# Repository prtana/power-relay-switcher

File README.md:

# Power Relay Switcher

**Power Relay Switcher** is an electronic device consisting of **4 relays**, each of which is capable of switching loads of up to **20 A**, **240 V AC** or **28 V DC**. Each of the four relays can be **manually** closed/opened from the **front panel** or via **USB** using **SCPI** commands. 

The device was designed for the automation of running battery pack management unit learning cycles for batteries up to a capacity of 200 Ah. In that application it is to be used in conjunction with a power supply, an electronic load and a multimeter. These battery learning cycles require charging-resting-discharging-resting periods in excess of 24 hours which are cumbersome for an operator to manually manage having to connect and disconnect a power supply and an electronic load at the exact moments determined by the learning cycle.

## User's Guide

### Front Panel
On the front panel there is a main **ON-OFF** rocker switch and **two toggle switches: USB/Manual** and **Close/Open** together with **two status LEDs** per relay. 

#### USB/Manual Switch
The **USB/Manual** switch allows the operator to choose whether the relay ought to be operated via **USB** using **SCPI** commands or **manually**. 

- If the **USB/Manual** switch is at the **USB** position, the **Close/Open** switch is disabled. 
- If the **USB/Manual** switch is switched from **USB** to **Manual**, the relay will be set to the position determined by the **Close/Open** switch. 
- If the **USB/Manual** switch is switched from **Manual** to **USB**, the relay will remain in the position last set by the **Close/Open** switch until a new **SCPI** command is sent to close or open it.

#### Close/Open Switch
The **Close/Open** switch allows the operator to manually close and open the relay contacts if the **USB/Manual** switch is at the **Manual** position. 

#### Status LEDs
There are two status LEDs per relay which indicate whether the relay contacts are in the **Closed** or **Open** position. 

### Rear Panel
On the rear panel there are:
- **USB Type-B** socket for SCPI control
- **Terminal blocks** with plugs for connecting to the relays' **Normally Open** (NO) and **Common** (COM) pins
- **Cooling fan**
- **230 V AC** mains C14 socket

### SCPI
The following SCPI commands are supported:

- `*IDN?\n`
- `ROUTe:CLOSe (<channel list>)\n`
- `ROUTe:CLOSe? (<channel list>)\n`
- `ROUTe:OPEN (<channel list>)\n`
- `ROUTe:OPEN? (<channel list>)\n`

`<channel list>` is a list of relay channels to be switched or queried. It can be a single channel, i.e `2`, a comma seperated list, i.e `2,4` or a range, i.e `1:3`.

#### \*IDN?\n
- Device identification query.
- Returns the vendor, model, serial number and firmware version in comma seperated format.
- Example `*IDN?\n` returns `Deeply Embedded,Power Relay Switcher,0,0\n`.

#### ROUTe:CLOSe (\<channel list\>)\n
- Closes the relays specified by the `<channel list\>`.
- The relay's **USB/Manual** switch has to be set to **USB** in order to switch it using SCPI.
- Returns nothing.
- Example to close relays one and four: `ROUT:CLOS (1,4)\n`

#### ROUTe:CLOSe? (\<channel list\>)\n
- Queries whether the relays specified by the `<channel list\>` are closed.
- Returns the status of queried relays in a comma seperated form, where 1 - closed, 0 - open.
- Example to query relays one to four: `ROUT:CLOS? (1:4)\n`; returns in case if relay one is closed and two to four are open: `1,0,0,0\n`.

#### ROUTe:OPEN (\<channel list\>)\n
- Opens the relays specified by the `<channel list\>`. 
- The relay's **USB/Manual** switch has to be set to **USB** in order to switch it using SCPI.
- Returns nothing.
- Example to open relays one to three: `ROUT:OPEN (1:3)\n`.

#### ROUTe:OPEN? (\<channel list\>)\n
- Queries whether the relays specified by the `<channel list\>` are open.
- Returns the status of queried relays in a comma seperated form, where 1 - open, 0 - closed.
- Example to query relays one to four: `ROUT:OPEN? (1:4)\n`; returns in case if relay one is closed and two to four are open: `0,1,1,1\n`.

#### Usage Example
- Determine the COM port in use.
- Use your preferred terminal program. In this case **PUTTY** is used, the COM port is `/dev/ttyACM1` and baudrate is selected `115200`. 

- For PUTTY, make sure to select `Force on` for `Local echo` and `Local line editing` to see the typed text and to send the whole line at once rather than character by character.

- Example comminucation is as follows. Note that a newline character `\n` can be entered in PUTTY by `Ctrl + J` and is displayed as `^J`.

## Project Overview

### Firmware
The C code for the STM32L062K8Tx microcontroller is in the [/firmware/power-relay-switcher](https://github.com/prtana/power-relay-switcher/tree/main/firmware/power-relay-switcher) directory.

### Hardware
There are relevant files in the [/hardware](https://github.com/prtana/power-relay-switcher/tree/main/hardware) directory for the three PCBs: the main PCB and the aluminium front and back panels.

#### Main PCB
For the main PCB the following resources are available:
- [3D step model](https://github.com/prtana/power-relay-switcher/tree/main/hardware/PRS_relay_board/3D)
- [Bill of materials](https://github.com/prtana/power-relay-switcher/tree/main/hardware/PRS_relay_board/BOM)
- [KiCad project](https://github.com/prtana/power-relay-switcher/tree/main/hardware/PRS_relay_board/KiCad)
- [Gerber files](https://github.com/prtana/power-relay-switcher/tree/main/hardware/PRS_relay_board/Gerbers)
- [PDF schematic](https://github.com/prtana/power-relay-switcher/blob/main/hardware/PRS_relay_board/PRS_relay_board.pdf)

#### Front Panel
For the aluminium front panel the following resources are available:
- [3D step model](https://github.com/prtana/power-relay-switcher/tree/main/hardware/PRS_front_panel/3D)
- [KiCad project](https://github.com/prtana/power-relay-switcher/tree/main/hardware/PRS_front_panel/KiCad)
- [Gerber files](https://github.com/prtana/power-relay-switcher/tree/main/hardware/PRS_front_panel/Gerbers)

#### Rear Panel
For the aluminium rear panel the following resources are available:
- [3D step model](https://github.com/prtana/power-relay-switcher/tree/main/hardware/PRS_rear_panel/3D)
- [KiCad project](https://github.com/prtana/power-relay-switcher/tree/main/hardware/PRS_rear_panel/KiCad)
- [Gerber files](https://github.com/prtana/power-relay-switcher/tree/main/hardware/PRS_rear_panel/Gerbers)

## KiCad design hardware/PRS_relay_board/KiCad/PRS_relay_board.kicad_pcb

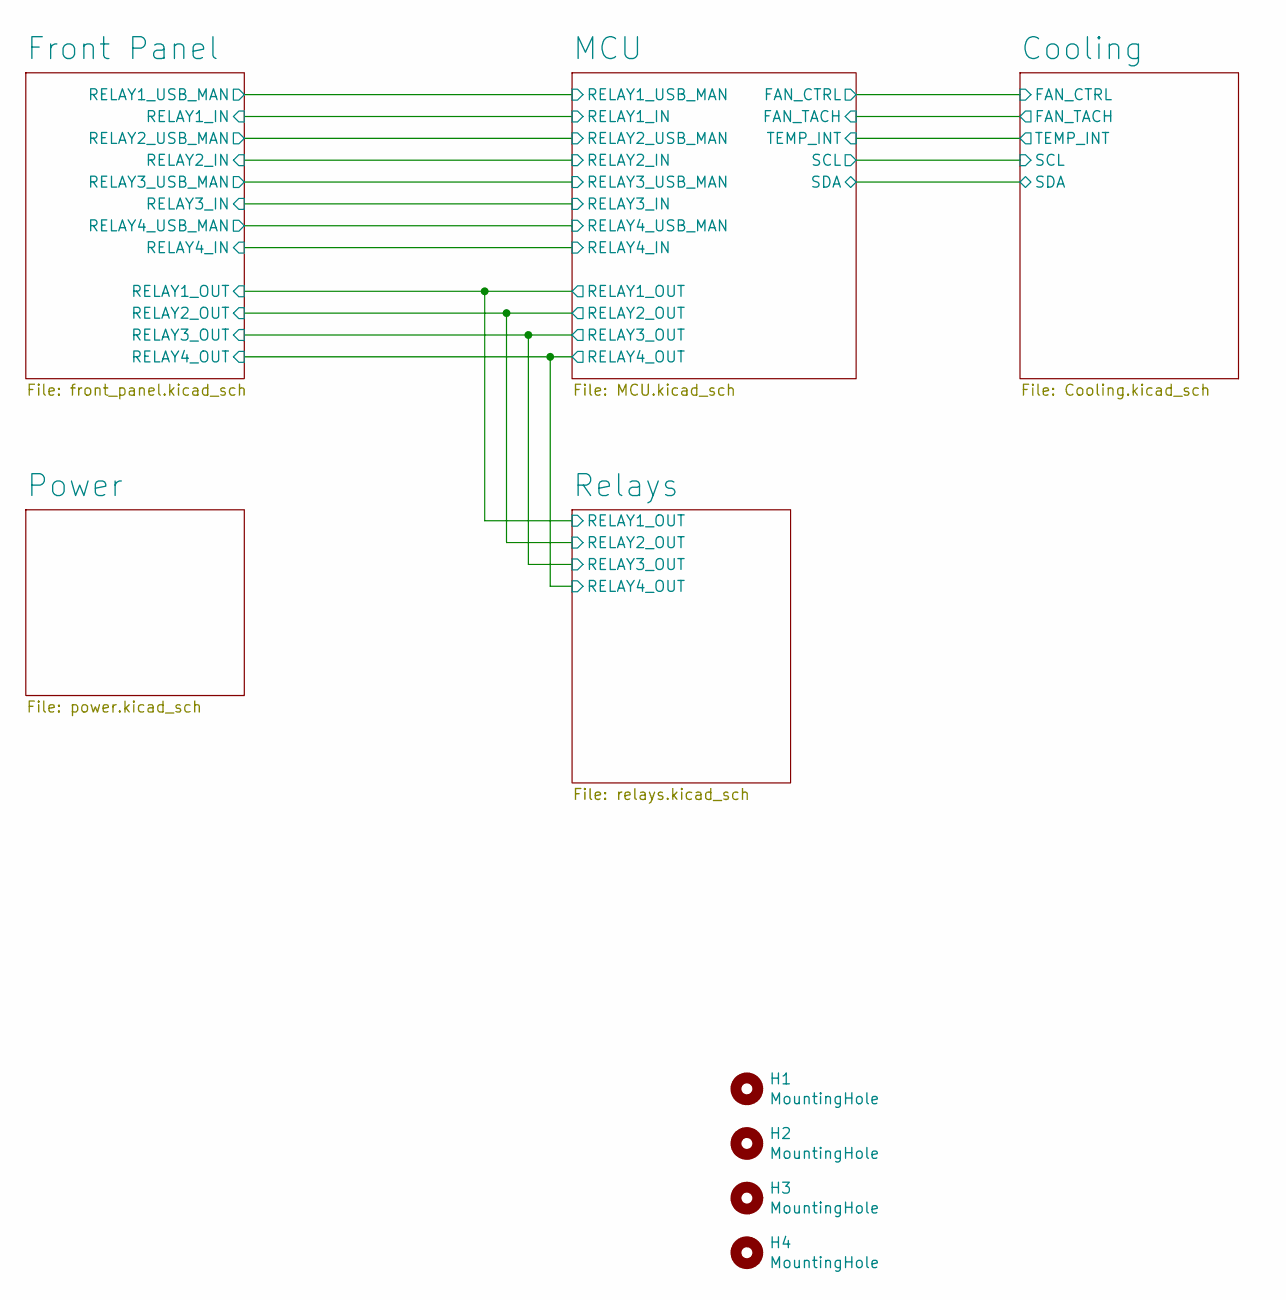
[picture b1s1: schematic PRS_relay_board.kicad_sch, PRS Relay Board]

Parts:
H1, H2, H3, H4: MountingHole; MountingHole_3.2mm_M3_DIN965

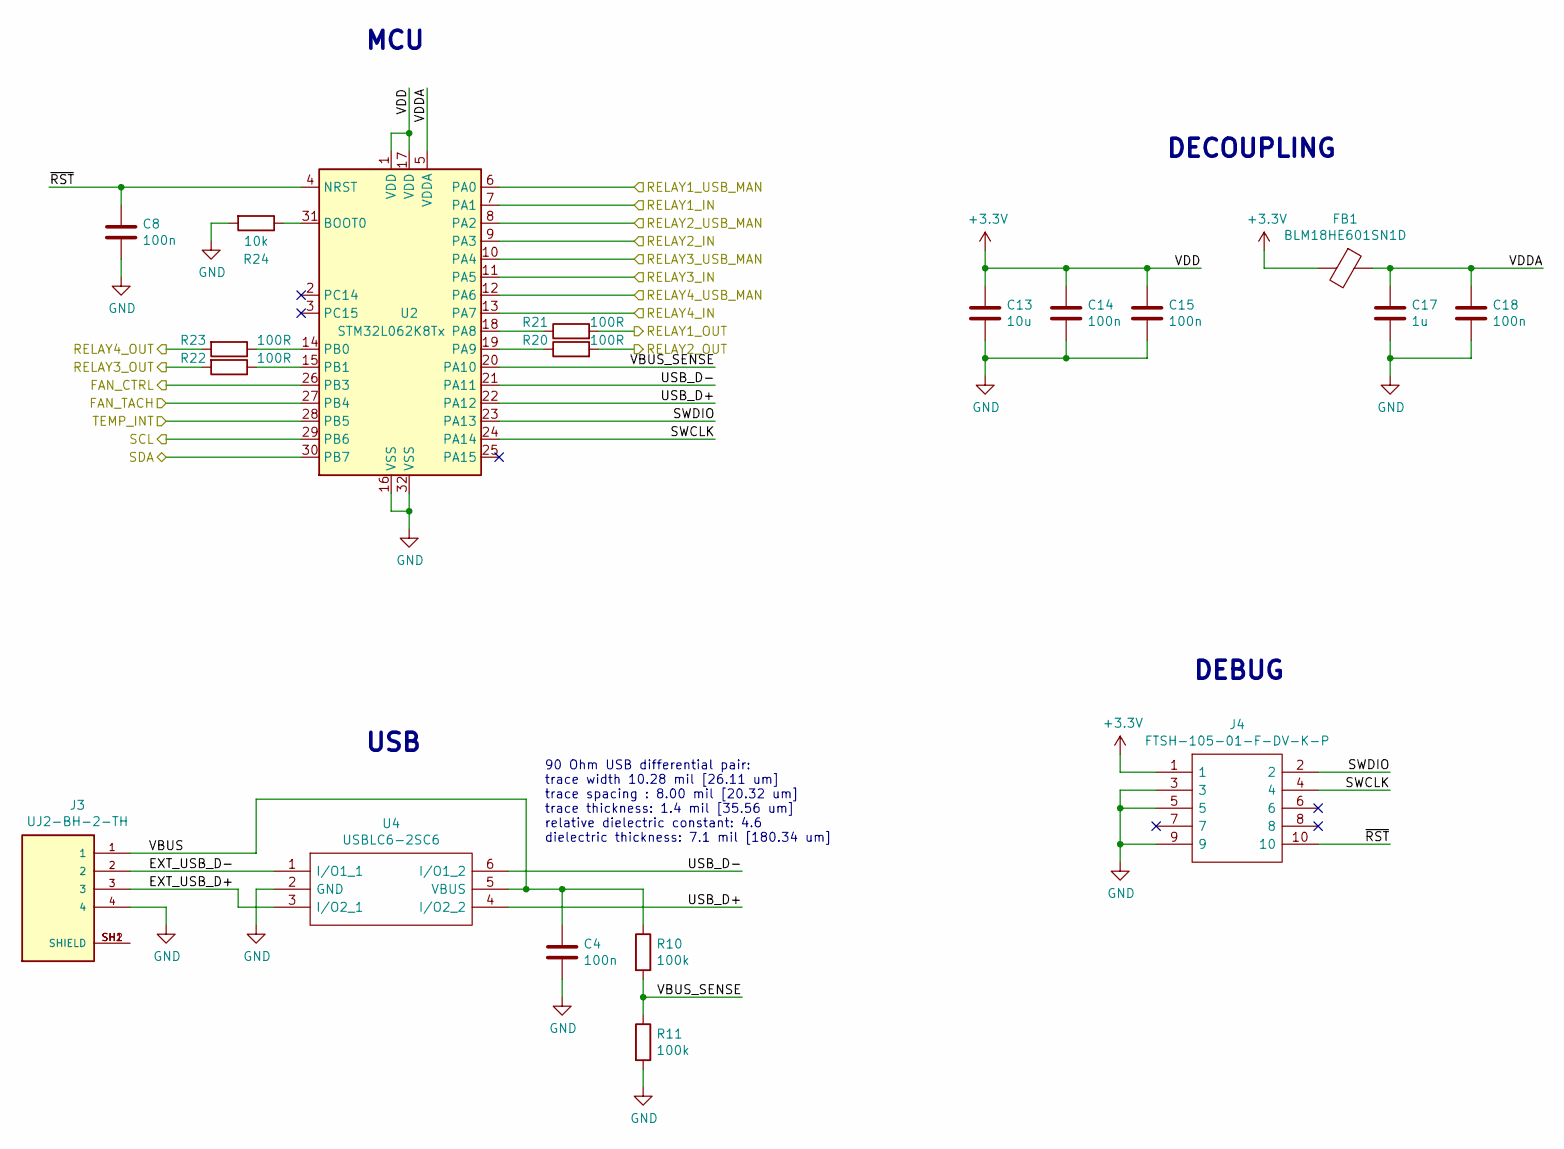
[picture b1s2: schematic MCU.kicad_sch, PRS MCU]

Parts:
C4, C8, C14, C15, C18: 100n; C_0603_1608Metric_Pad1.08x0.95mm_HandSolder
C13: 10u; C_1206_3216Metric_Pad1.33x1.80mm_HandSolder
C17: 1u; C_0603_1608Metric_Pad1.08x0.95mm_HandSolder
FB1: BLM18HE601SN1D; R_0603_1608Metric_Pad0.98x0.95mm_HandSolder
J3: UJ2-BH-2-TH; CUI_UJ2-BH-2-TH; PART_REV 1.0
J4: FTSH-105-01-F-DV-K-P; FTSH-105-XX-YYY-DV-K-P; Manufacturer_Part_Number FTSH-105-01-F-DV-K-P; Mouser Part Number 200-FTSH10501FDVKP
R10, R11: 100k; R_0603_1608Metric_Pad0.98x0.95mm_HandSolder
R20, R21, R22, R23: 100R; R_0603_1608Metric_Pad0.98x0.95mm_HandSolder
R24: 10k; R_0603_1608Metric_Pad0.98x0.95mm_HandSolder
U2: STM32L062K8Tx; LQFP-32_7x7mm_P0.8mm
U4: USBLC6-2SC6; SOT95P280X145-6N; Manufacturer_Part_Number USBLC6-2SC6; Mouser Part Number 511-USBLC6-2SC6

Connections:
+3V3: C13.1, C14.1, C15.1, FB1.2, J4.1, U2.1 (VDD), U2.17 (VDD); also elsewhere on the board
/Cooling/FAN_CTRL: U2.26 (PB3); also elsewhere on the board
/Cooling/FAN_TACH: U2.27 (PB4); also elsewhere on the board
/Cooling/SCL: U2.29 (PB6); also elsewhere on the board
/Cooling/SDA: U2.30 (PB7); also elsewhere on the board
/Cooling/TEMP_INT: U2.28 (PB5); also elsewhere on the board
/Front Panel/RELAY1_IN: U2.7 (PA1); also elsewhere on the board
/Front Panel/RELAY1_OUT: R21.2; also elsewhere on the board
/Front Panel/RELAY1_USB_MAN: U2.6 (PA0); also elsewhere on the board
/Front Panel/RELAY2_IN: U2.9 (PA3); also elsewhere on the board
/Front Panel/RELAY2_OUT: R20.2; also elsewhere on the board
/Front Panel/RELAY2_USB_MAN: U2.8 (PA2); also elsewhere on the board
/Front Panel/RELAY3_IN: U2.11 (PA5); also elsewhere on the board
/Front Panel/RELAY3_OUT: R22.2; also elsewhere on the board
/Front Panel/RELAY3_USB_MAN: U2.10 (PA4); also elsewhere on the board
/Front Panel/RELAY4_IN: U2.13 (PA7); also elsewhere on the board
/Front Panel/RELAY4_OUT: R23.2; also elsewhere on the board
/Front Panel/RELAY4_USB_MAN: U2.12 (PA6); also elsewhere on the board
/MCU/EXT_USB_D+: J3.3, U4.3 (I/O2_1)
/MCU/EXT_USB_D-: J3.2, U4.1 (I/O1_1)
/MCU/SWCLK: J4.4, U2.24 (PA14)
/MCU/SWDIO: J4.2, U2.23 (PA13)
/MCU/USB_D+: U2.22 (PA12), U4.4 (I/O2_2)
/MCU/USB_D-: U2.21 (PA11), U4.6 (I/O1_2)
/MCU/VBUS: C4.1, J3.1, R10.1, U4.5 (VBUS)
/MCU/VBUS_SENSE: R10.2, R11.1, U2.20 (PA10)
/MCU/VDDA: C17.1, C18.1, FB1.1, U2.5 (VDDA)
/MCU/~RST: C8.1, J4.10, U2.4 (NRST)
GND: C4.2, C8.2, C13.2, C14.2, C15.2, C17.2, C18.2, J3.4, J4.3, J4.5, J4.9, R11.2, R24.2, U2.16 (VSS), U2.32 (VSS), U4.2 (GND); also elsewhere on the board
unnamed: J3.SH1 (SHIELD), J3.SH2 (SHIELD)
unnamed: R20.1, U2.19 (PA9)
unnamed: R21.1, U2.18 (PA8)
unnamed: R22.1, U2.15 (PB1)
unnamed: R23.1, U2.14 (PB0)
unnamed: R24.1, U2.31 (BOOT0)

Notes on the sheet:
DEBUG
90 Ohm USB differential pair: trace width 10.28 mil [26.11 um] trace spacing : 8.00 mil [20.32 um] trace thickness: 1.4 mil [35.56 um] relative dielectric constant: 4.6 dielectric thickness: 7.1 mil [180.34 um]
USB
MCU
DECOUPLING

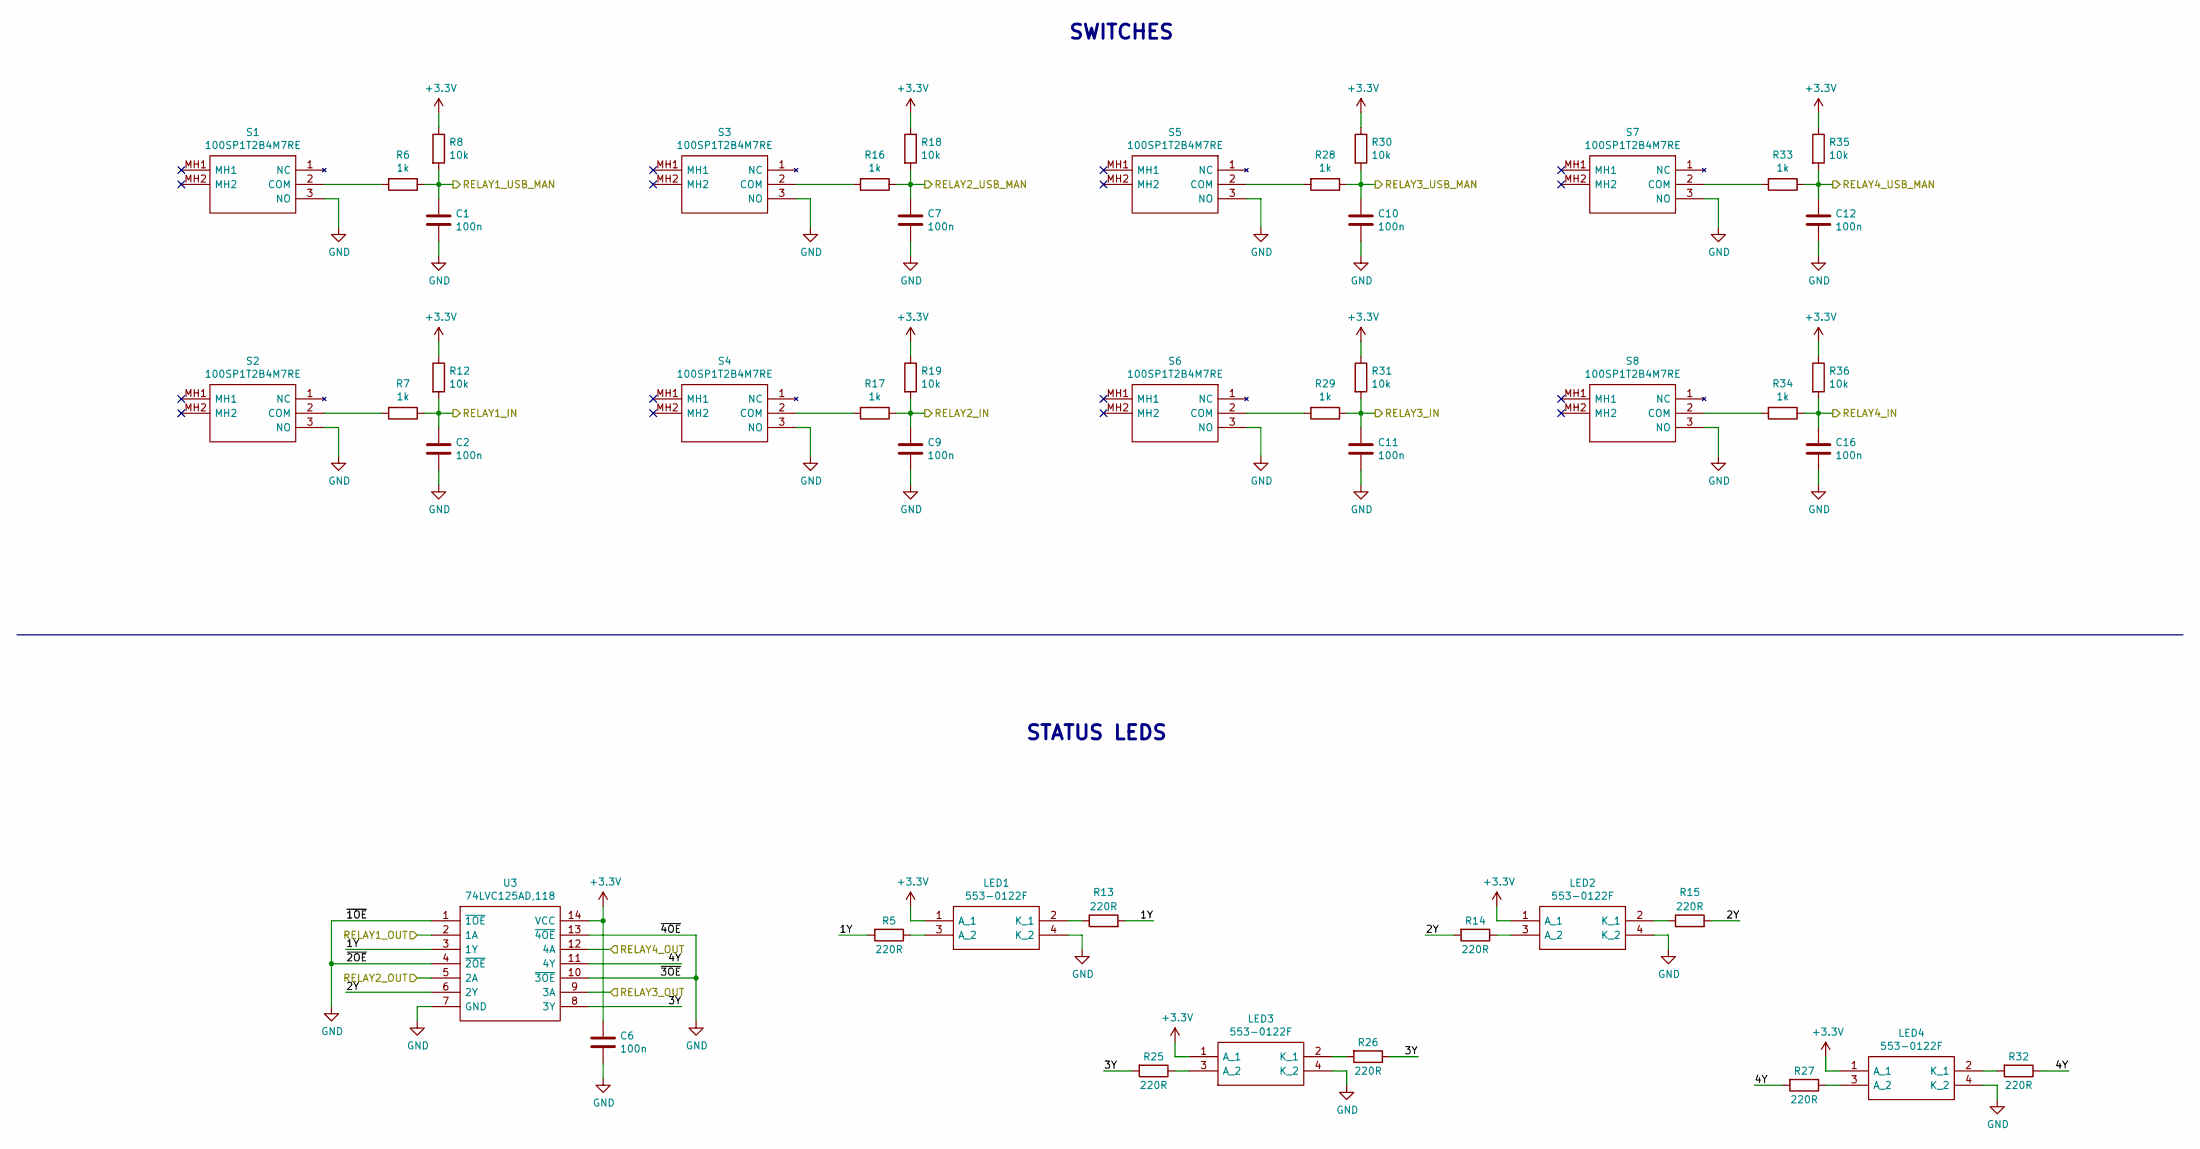
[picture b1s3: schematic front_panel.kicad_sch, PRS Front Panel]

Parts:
C1, C2, C6, C7, C9, C10, C11, C12, C16: 100n; C_0603_1608Metric_Pad1.08x0.95mm_HandSolder
LED1, LED2, LED3, LED4: 553-0122F; 5530122F; Manufacturer_Part_Number 553-0122F; Mouser Part Number 645-553-0122F
R5, R13, R14, R15, R25, R26, R27, R32: 220R; R_0603_1608Metric_Pad0.98x0.95mm_HandSolder
R6, R7, R16, R17, R28, R29, R33, R34: 1k; R_0603_1608Metric_Pad0.98x0.95mm_HandSolder
R8, R12, R18, R19, R30, R31, R35, R36: 10k; R_0603_1608Metric_Pad0.98x0.95mm_HandSolder
S1, S2, S3, S4, S5, S6, S7, S8: 100SP1T2B4M7RE; Manufacturer_Part_Number 100SP1T2B4M7RE; Mouser Part Number 612-100-A2472
U3: 74LVC125AD,118; SOIC127P600X175-14N; Manufacturer_Part_Number 74LVC125AD,118; Mouser Part Number 771-74LVC125AD-T

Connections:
+3V3: C6.1, LED1.1 (A_1), LED2.1 (A_1), LED3.1 (A_1), LED4.1 (A_1), R8.1, R12.1, R18.1, R19.1, R30.1, R31.1, R35.1, R36.1, U3.14 (VCC); also elsewhere on the board
/Front Panel/1Y: R5.2, R13.2, U3.3 (1Y)
/Front Panel/2Y: R14.2, R15.2, U3.6 (2Y)
/Front Panel/3Y: R25.2, R26.1, U3.8 (3Y)
/Front Panel/4Y: R27.2, R32.1, U3.11 (4Y)
/Front Panel/RELAY1_IN: C2.1, R7.1, R12.2; also elsewhere on the board
/Front Panel/RELAY1_OUT: U3.2 (1A); also elsewhere on the board
/Front Panel/RELAY1_USB_MAN: C1.1, R6.1, R8.2; also elsewhere on the board
/Front Panel/RELAY2_IN: C9.1, R17.1, R19.2; also elsewhere on the board
/Front Panel/RELAY2_OUT: U3.5 (2A); also elsewhere on the board
/Front Panel/RELAY2_USB_MAN: C7.1, R16.1, R18.2; also elsewhere on the board
/Front Panel/RELAY3_IN: C11.1, R29.1, R31.2; also elsewhere on the board
/Front Panel/RELAY3_OUT: U3.9 (3A); also elsewhere on the board
/Front Panel/RELAY3_USB_MAN: C10.1, R28.1, R30.2; also elsewhere on the board
/Front Panel/RELAY4_IN: C16.1, R34.1, R36.2; also elsewhere on the board
/Front Panel/RELAY4_OUT: U3.12 (4A); also elsewhere on the board
/Front Panel/RELAY4_USB_MAN: C12.1, R33.1, R35.2; also elsewhere on the board
GND: C1.2, C2.2, C6.2, C7.2, C9.2, C10.2, C11.2, C12.2, C16.2, LED1.4 (K_2), LED2.4 (K_2), LED3.4 (K_2), LED4.4 (K_2), S1.3 (NO), S2.3 (NO), S3.3 (NO), S4.3 (NO), S5.3 (NO), S6.3 (NO), S7.3 (NO), S8.3 (NO), U3.1 (~1OE), U3.4 (~2OE), U3.7 (GND), U3.10 (~3OE), U3.13 (~4OE); also elsewhere on the board
unnamed: LED1.2 (K_1), R13.1
unnamed: LED1.3 (A_2), R5.1
unnamed: LED2.2 (K_1), R15.1
unnamed: LED2.3 (A_2), R14.1
unnamed: LED3.2 (K_1), R26.2
unnamed: LED3.3 (A_2), R25.1
unnamed: LED4.2 (K_1), R32.2
unnamed: LED4.3 (A_2), R27.1
unnamed: R6.2, S1.2 (COM)
unnamed: R7.2, S2.2 (COM)
unnamed: R16.2, S3.2 (COM)
unnamed: R17.2, S4.2 (COM)
unnamed: R28.2, S5.2 (COM)
unnamed: R29.2, S6.2 (COM)
unnamed: R33.2, S7.2 (COM)
unnamed: R34.2, S8.2 (COM)

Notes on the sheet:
STATUS LEDS
SWITCHES

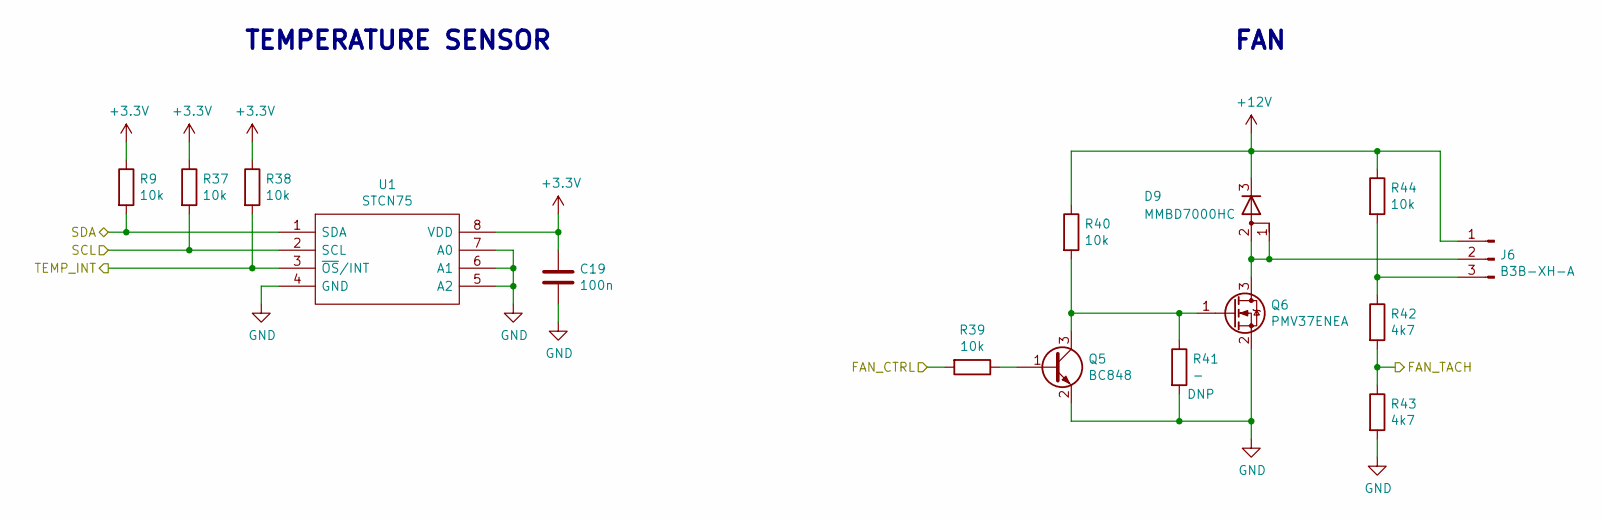
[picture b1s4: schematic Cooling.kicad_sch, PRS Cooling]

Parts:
C19: 100n; C_0603_1608Metric_Pad1.08x0.95mm_HandSolder
D9: MMBD7000HC; SOT-23_Handsoldering
J6: B3B-XH-A; JST_XH_B3B-XH-A_1x03_P2.50mm_Vertical
Q5: BC848; SOT-23_Handsoldering
Q6: PMV37ENEA; SOT-23_Handsoldering
R9, R37, R38, R39, R40, R44: 10k; R_0603_1608Metric_Pad0.98x0.95mm_HandSolder
R41: -; R_0603_1608Metric_Pad0.98x0.95mm_HandSolder
R42, R43: 4k7; R_0603_1608Metric_Pad0.98x0.95mm_HandSolder
U1: STCN75; SOP65P490X110-8N; Manufacturer_Part_Number STCN75

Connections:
+3V3: C19.1, R9.1, R37.1, R38.1, U1.8 (VDD); also elsewhere on the board
+12V: D9.3 (K), J6.1, R40.1, R44.1; also elsewhere on the board
/Cooling/FAN_CTRL: R39.2; also elsewhere on the board
/Cooling/FAN_TACH: R42.2, R43.1; also elsewhere on the board
/Cooling/SCL: R37.2, U1.2 (SCL); also elsewhere on the board
/Cooling/SDA: R9.2, U1.1 (SDA); also elsewhere on the board
/Cooling/TEMP_INT: R38.2, U1.3 (~OS/INT); also elsewhere on the board
GND: C19.2, Q5.2 (E), Q6.2 (S), R41.2, R43.2, U1.4 (GND), U1.5 (A2), U1.6 (A1), U1.7 (A0); also elsewhere on the board
unnamed: D9.1 (A), D9.2 (A), J6.2, Q6.3 (D)
unnamed: J6.3, R42.1, R44.2
unnamed: Q5.1 (B), R39.1
unnamed: Q5.3 (C), Q6.1 (G), R40.2, R41.1

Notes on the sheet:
FAN
TEMPERATURE SENSOR

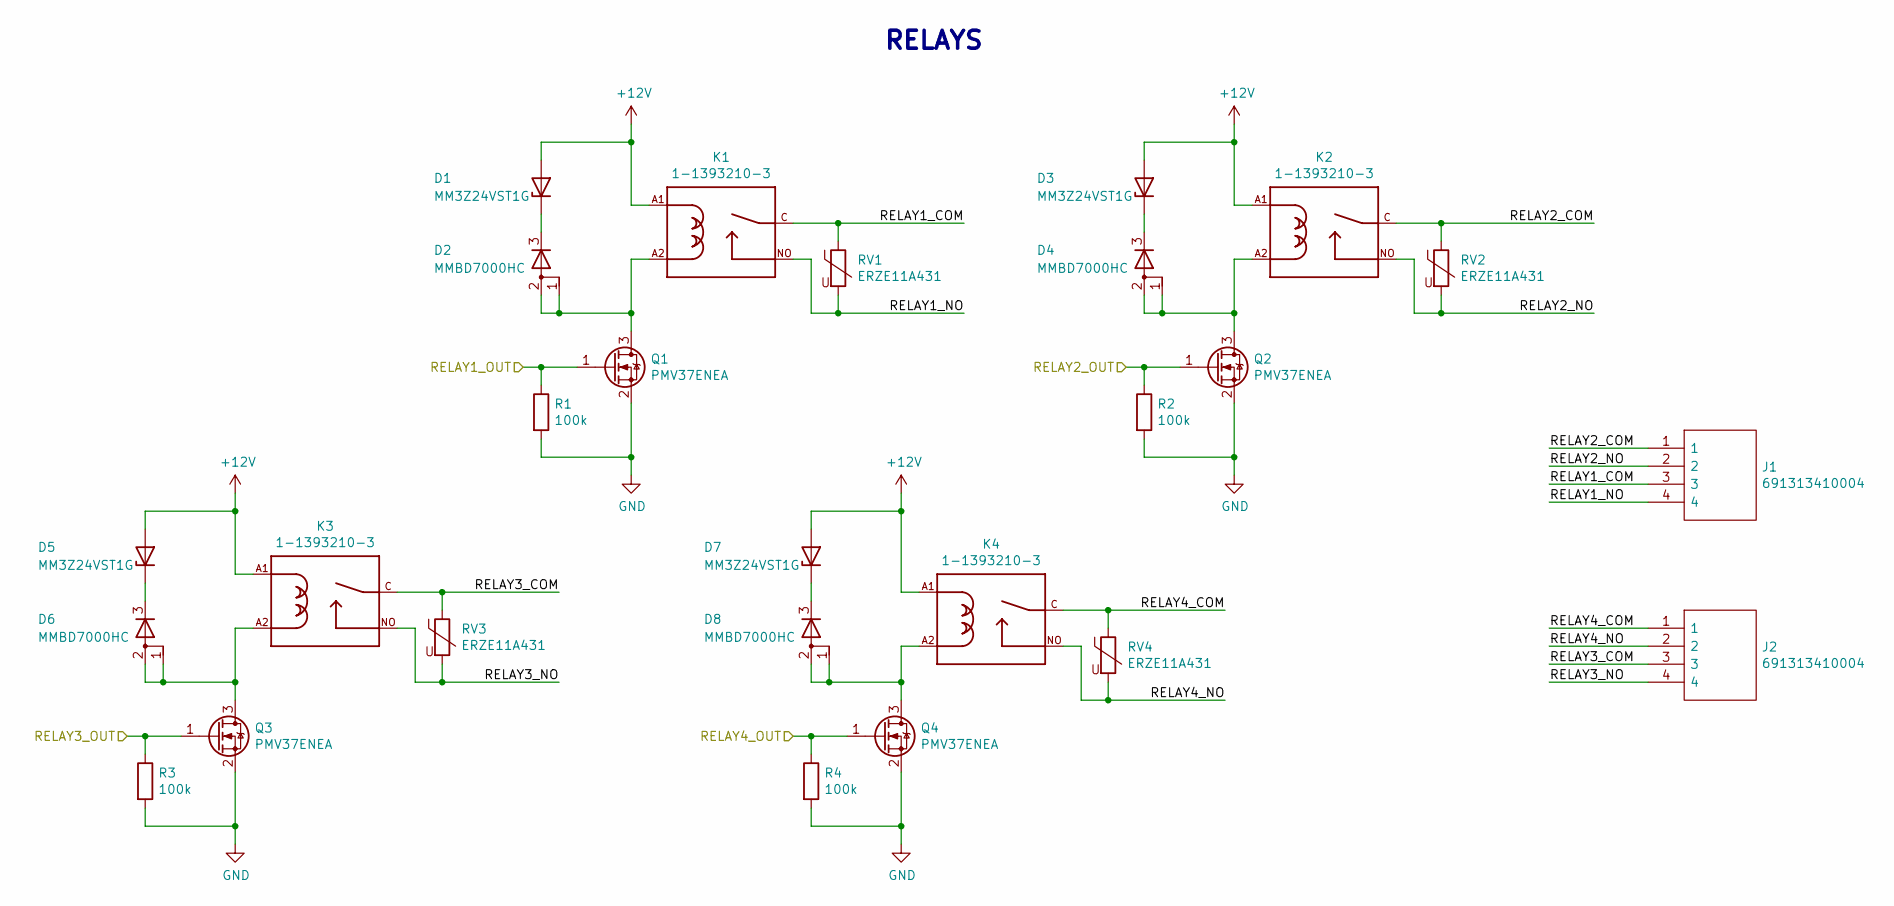
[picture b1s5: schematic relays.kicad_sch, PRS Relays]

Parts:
D1, D3, D5, D7: MM3Z24VST1G; D_SOD-323
D2, D4, D6, D8: MMBD7000HC; SOT-23_Handsoldering
J1, J2: 691313410004; Manufacturer_Part_Number 691313410004; Mouser Part Number 710-691313410004
K1, K2, K3, K4: 1-1393210-3; TE_1-1393210-3
Q1, Q2, Q3, Q4: PMV37ENEA; SOT-23_Handsoldering
R1, R2, R3, R4: 100k; R_0603_1608Metric_Pad0.98x0.95mm_HandSolder
RV1, RV2, RV3, RV4: ERZE11A431; RV_Disc_D12mm_W6.3mm_P7.5mm

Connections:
+12V: D1.2 (A), D3.2 (A), D5.2 (A), D7.2 (A), K1.A1, K2.A1, K3.A1, K4.A1; also elsewhere on the board
/Front Panel/RELAY1_OUT: Q1.1 (G), R1.1; also elsewhere on the board
/Front Panel/RELAY2_OUT: Q2.1 (G), R2.1; also elsewhere on the board
/Front Panel/RELAY3_OUT: Q3.1 (G), R3.1; also elsewhere on the board
/Front Panel/RELAY4_OUT: Q4.1 (G), R4.1; also elsewhere on the board
/Relays/RELAY1_COM: J1.3, K1.C, RV1.1
/Relays/RELAY1_NO: J1.4, K1.NO, RV1.2
/Relays/RELAY2_COM: J1.1, K2.C, RV2.1
/Relays/RELAY2_NO: J1.2, K2.NO, RV2.2
/Relays/RELAY3_COM: J2.3, K3.C, RV3.1
/Relays/RELAY3_NO: J2.4, K3.NO, RV3.2
/Relays/RELAY4_COM: J2.1, K4.C, RV4.1
/Relays/RELAY4_NO: J2.2, K4.NO, RV4.2
GND: Q1.2 (S), Q2.2 (S), Q3.2 (S), Q4.2 (S), R1.2, R2.2, R3.2, R4.2; also elsewhere on the board
unnamed: D1.1 (K), D2.3 (K)
unnamed: D2.1 (A), D2.2 (A), K1.A2, Q1.3 (D)
unnamed: D3.1 (K), D4.3 (K)
unnamed: D4.1 (A), D4.2 (A), K2.A2, Q2.3 (D)
unnamed: D5.1 (K), D6.3 (K)
unnamed: D6.1 (A), D6.2 (A), K3.A2, Q3.3 (D)
unnamed: D7.1 (K), D8.3 (K)
unnamed: D8.1 (A), D8.2 (A), K4.A2, Q4.3 (D)

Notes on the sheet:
RELAYS

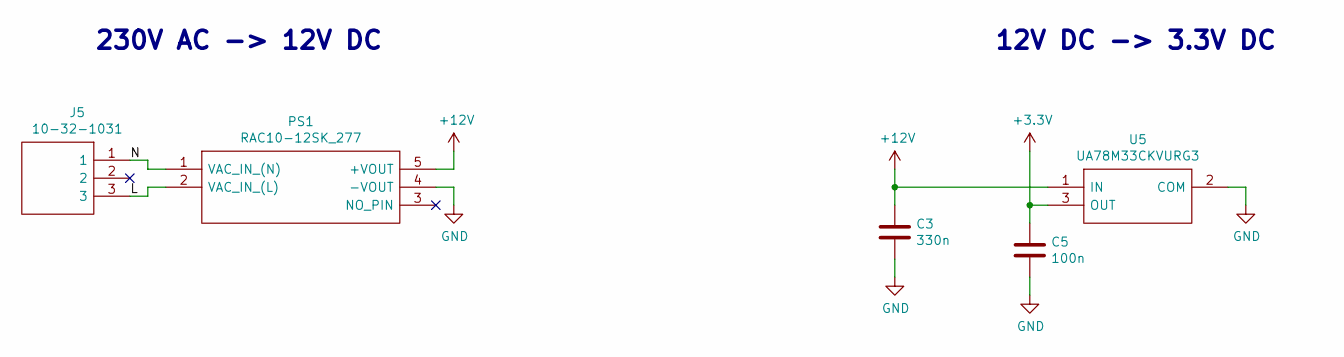
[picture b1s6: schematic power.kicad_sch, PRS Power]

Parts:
C3: 330n; C_0603_1608Metric_Pad1.08x0.95mm_HandSolder
C5: 100n; C_0603_1608Metric_Pad1.08x0.95mm_HandSolder
J5: 10-32-1031; SHDR3W114P0X508_1X3_1416X1140X1425P; Manufacturer_Part_Number 10-32-1031; Mouser Part Number 538-10-32-1031
PS1: RAC10-12SK_277; Manufacturer_Part_Number RAC10-12SK/277; Mouser Part Number 919-RAC10-12SK/277
U5: UA78M33CKVURG3; TPS7A6533QKVURQ1; Manufacturer_Part_Number UA78M33CKVURG3; Mouser Part Number 595-UA78M33CKVURG3

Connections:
+3V3: C5.1, U5.3 (OUT); also elsewhere on the board
+12V: C3.1, PS1.5 (+VOUT), U5.1 (IN); also elsewhere on the board
/Power/L: J5.3, PS1.2 (VAC_IN_(L))
/Power/N: J5.1, PS1.1 (VAC_IN_(N))
GND: C3.2, C5.2, PS1.4 (-VOUT), U5.2 (COM); also elsewhere on the board

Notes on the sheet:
12V DC -> 3.3V DC
230V AC -> 12V DC

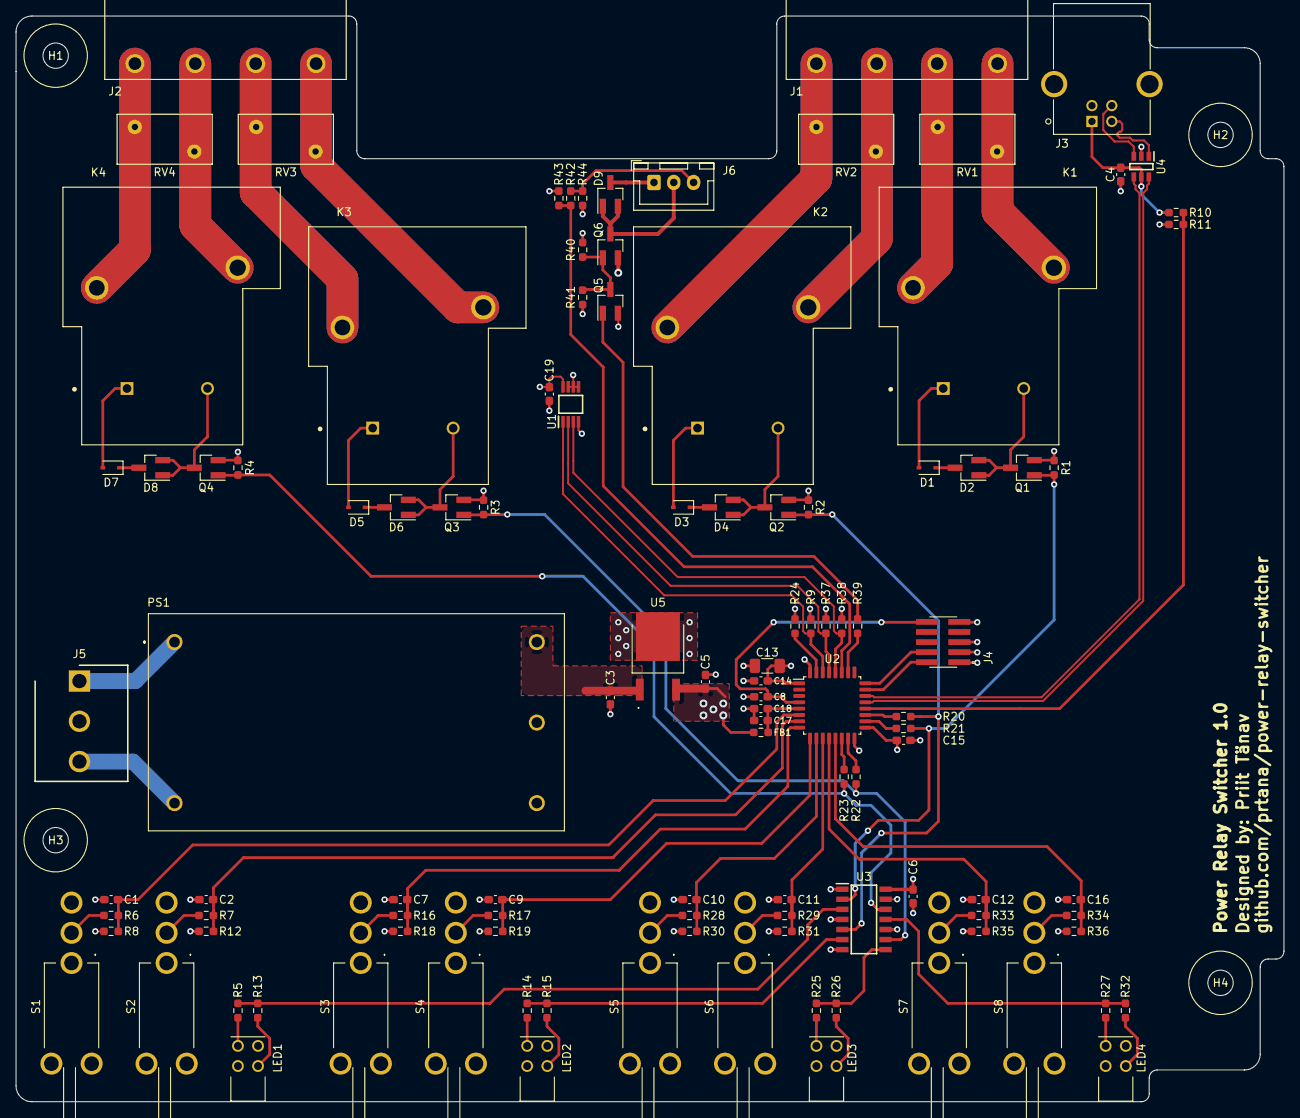
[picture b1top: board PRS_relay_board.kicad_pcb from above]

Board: 4 copper layers, 160.0 x 137.0 mm, 115 parts (0 on the bottom side), 78 nets.
